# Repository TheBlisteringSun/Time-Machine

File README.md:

# Time-Machine
Deceptively small macropad (could fit in your palm)

Time Machine is a KMK-powered, 6-key + Rotary Encoder, OLED display, Macropad with underglow lighting. 

KMK firmware for the custom Hackpad
-----------------------------------
Features
~~~~~~~~
* Constants at the top define which matrix key does what—easy to tweak later.
* A sleep toggle (OLED off, inputs ignored until woken).
* EC11 rotary encoder (GP8=A, GP9=B, GP10=SW)
    * Short‑press once → enter **Timer‑Setup** mode
    * Turn knob → cycle through preset durations
      (1, 5, 10, 15, 20, 30, 40 minutes)
    * Short‑press again → start the countdown
* 0.91″ SSD1306 OLED (I²C on GP6=SDA, GP7=SCL)
    * Shows selected duration or live progress bar + remaining time
* 3× SK6812 LEDs daisy‑chained on GP5 (optional flash on timer end)
* Stores a persistent points counter in /points.txt and flashes the LEDs:
    * +1 → yellow flash
    * +2 → purple for 1 minute
    * negative actions → blue flash
 * Two under‑glow LEDs stay dim green whenever no other colour is flashing.
~~~~~~~~~~

Requires:
* CircuitPython ≥ 9.0 or RP2040‑UF2 w/ displayio support
* `adafruit_displayio_ssd1306` and `adafruit_display_text` libraries in /lib
* KMK (copy kmk/ into CIRCUITPY drive)

Save this file as `code.py` or `main.py` on the XIAO‑RP2040.

# Design
This was my first time doing a hardware project! Thanks to all the friends that I bugged constantly :P

## PCB
I learned how to use a matrix to get all my features onto the XIAO microcontroller perfectly

The schematic and the PCB were made in KiCad

## Case
First time CADing too! It ain't much, but it's honest work.

Case was made using Autodesk Fusion

## Firmware
Time Machine was made with custom-coded firmware written with the KMK library in Python

# BOM
*6 cans of redbull not included

## Electronics
* 1x XIAO RP2040
* 1x EC11E Rotary Encoder (with switch)
* 1x Rotary Encoder Knob
* 1x 0.91" OLED Display
* 6x Cherry MX Switches
* 6x Blank DSA Keycaps
* 6x Diode (THT)
* 3x SK6812 Mini LEDs
* 1x 330 Ohm Resistor

## Case
* 1x case_top.stl
* 1x case_plt.stl
* 1x case_btm.stl
* 3x M3x16 screw
* 4x 10mm Rubber Feet
* 3x M3x5x4mm heatset inserts

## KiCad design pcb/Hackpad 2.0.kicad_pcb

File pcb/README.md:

# PCB
This file contains all the libraries used to make the PCB for the Time Machine

The gerbers.zip file to make your own PCB can be found in \production

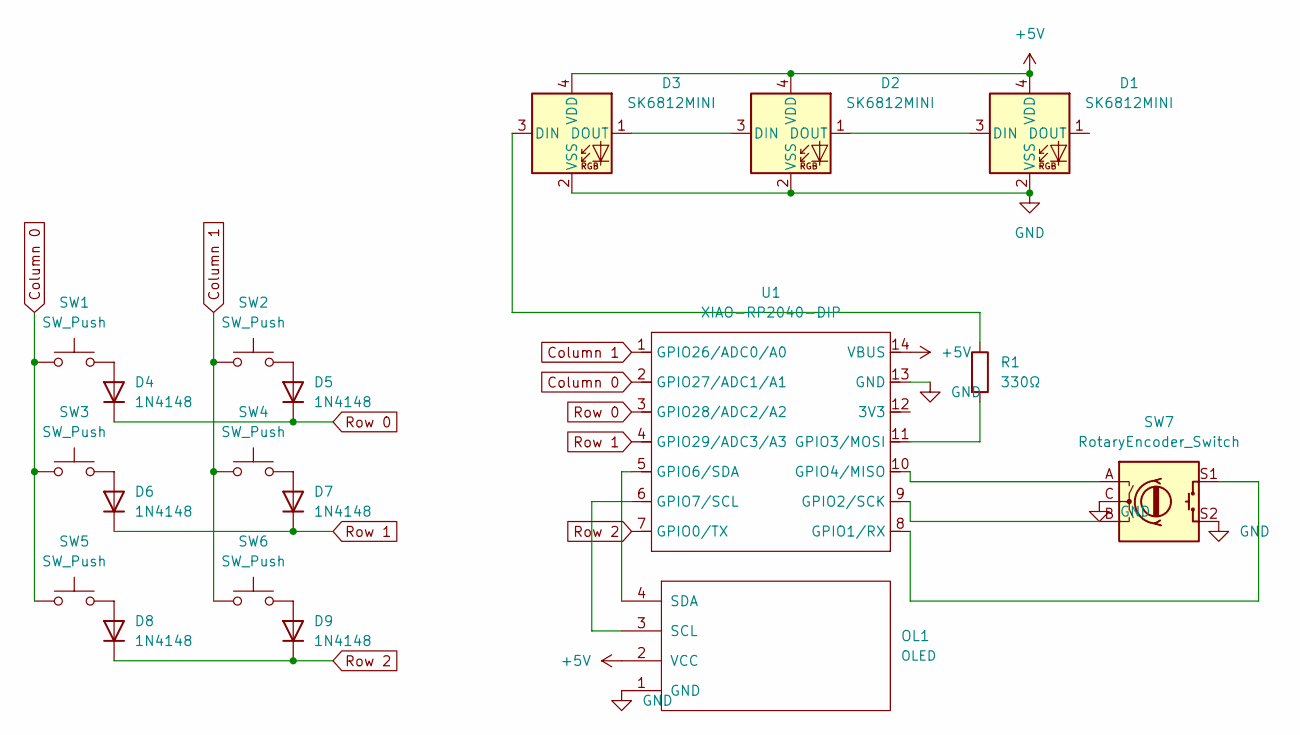
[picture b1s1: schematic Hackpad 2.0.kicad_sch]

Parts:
D1, D2, D3: SK6812MINI; LED_SK6812MINI_PLCC4_3.5x3.5mm_P1.75mm
D4, D5, D6, D7, D8, D9: 1N4148; D_DO-35_SOD27_P7.62mm_Horizontal
OL1: OLED; SSD1306-0.91-OLED-4pin-128x32
R1: 330Ω; R_Axial_DIN0207_L6.3mm_D2.5mm_P7.62mm_Horizontal
SW1, SW2, SW3, SW4, SW5, SW6: SW_Push; SW_Cherry_MX_1.00u_PCB
SW7: RotaryEncoder_Switch; RotaryEncoder_Alps_EC11E-Switch_Vertical_H20mm
U1: XIAO-RP2040-DIP

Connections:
+5V: D1.4 (VDD), D2.4 (VDD), D3.4 (VDD), OL1.2 (VCC), U1.14 (VBUS)
Column 0: SW1.1, SW3.1, SW5.1, U1.2 (GPIO27/ADC1/A1)
Column 1: SW2.1, SW4.1, SW6.1, U1.1 (GPIO26/ADC0/A0)
GND: D1.2 (VSS), D2.2 (VSS), D3.2 (VSS), OL1.1 (GND), SW7.C, SW7.S2, U1.13 (GND)
unnamed: D1.3 (DIN), D2.1 (DOUT)
unnamed: D2.3 (DIN), D3.1 (DOUT)
unnamed: D3.3 (DIN), R1.1
unnamed: D4.2 (A), SW1.2
unnamed: D5.2 (A), SW2.2
unnamed: D6.2 (A), SW3.2
unnamed: D7.2 (A), SW4.2
unnamed: D8.2 (A), SW5.2
unnamed: D9.2 (A), SW6.2
unnamed: OL1.3 (SCL), U1.6 (GPIO7/SCL)
unnamed: OL1.4 (SDA), U1.5 (GPIO6/SDA)
unnamed: SW7.S1, U1.8 (GPIO1/RX)
unnamed: SW7.B, U1.9 (GPIO2/SCK)
unnamed: R1.2, U1.11 (GPIO3/MOSI)
unnamed: SW7.A, U1.10 (GPIO4/MISO)
Row 0: D4.1 (K), D5.1 (K), U1.3 (GPIO28/ADC2/A2)
Row 1: D6.1 (K), D7.1 (K), U1.4 (GPIO29/ADC3/A3)
Row 2: D8.1 (K), D9.1 (K), U1.7 (GPIO0/TX)

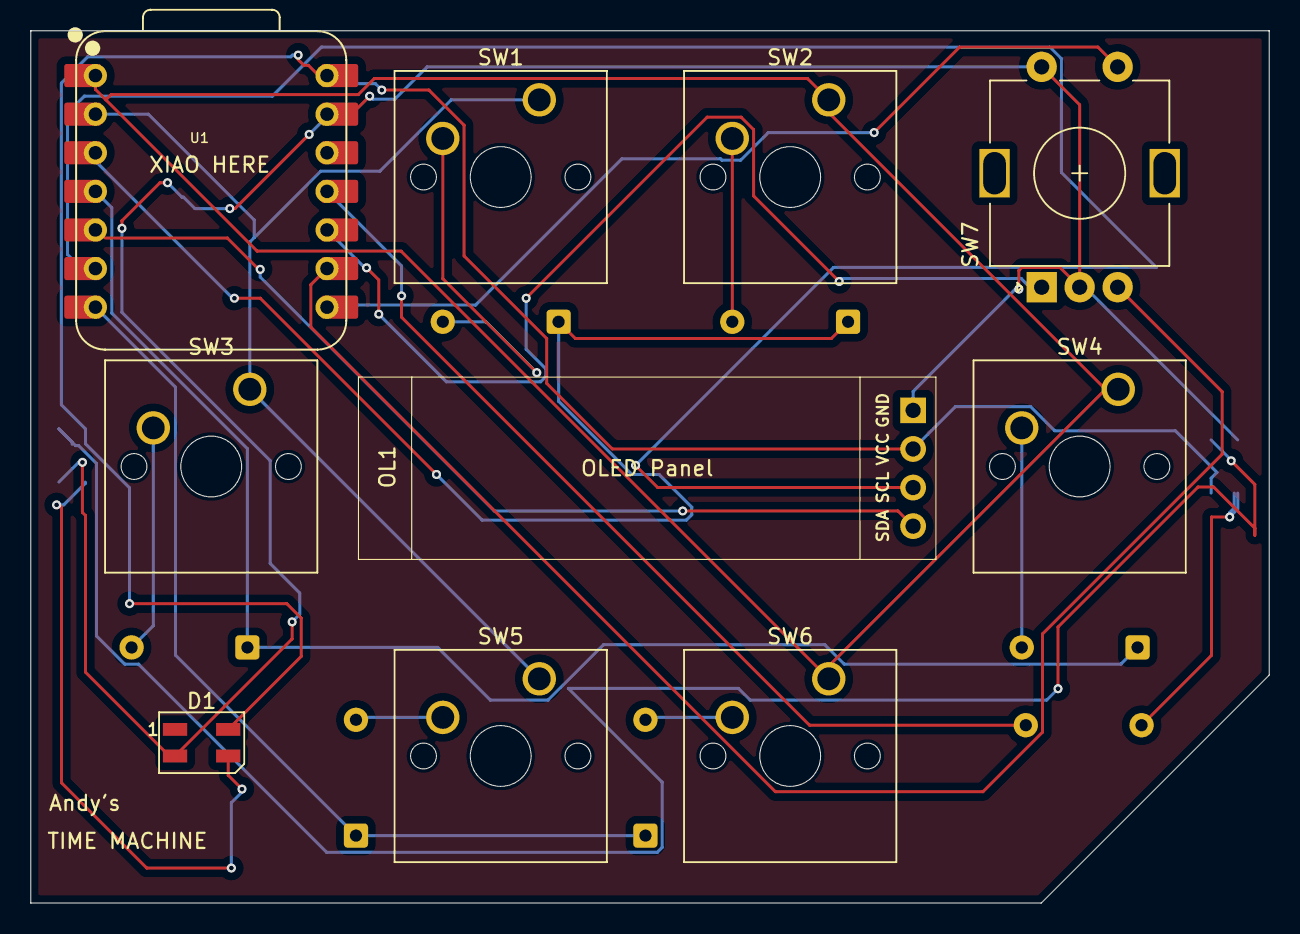
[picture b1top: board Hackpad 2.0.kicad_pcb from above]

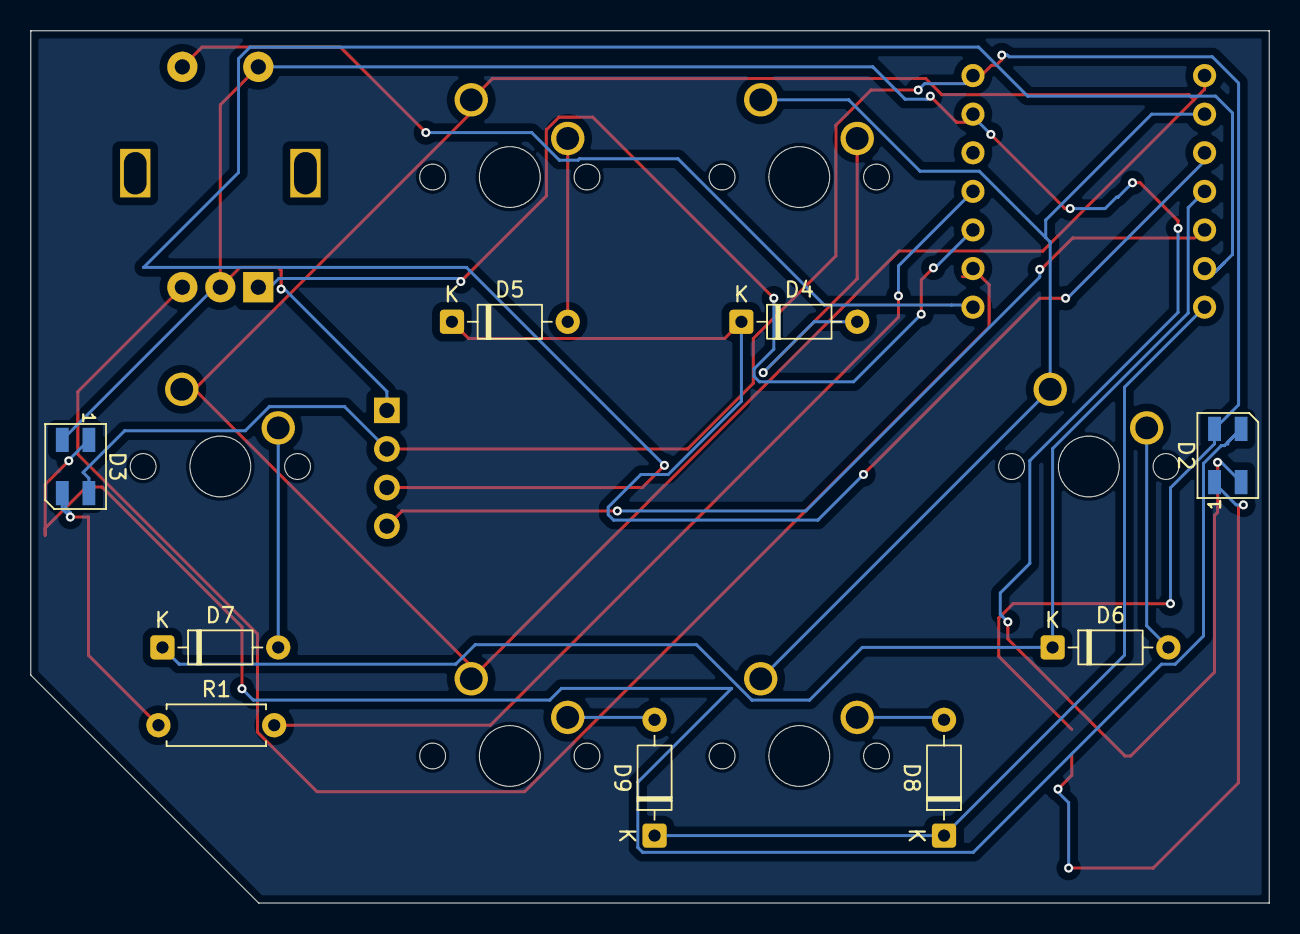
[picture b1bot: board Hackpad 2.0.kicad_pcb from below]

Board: 2 copper layers, 81.5 x 57.4 mm, 19 parts (9 on the bottom side), 22 nets.

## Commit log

2025-06-16 update features
2025-06-16 Update README.md
    PCB, Case, Firmware, BOM
2025-06-16 Add gerbers file
2025-06-16 Rename gerbers.zip to production/gerbers.zip
2025-06-16 add headset inserts
2025-06-16 add case
2025-06-16 Update and rename main.py to code.py
    Add functions to each button + Sleep + underglow
2025-06-16 Add PCB
2025-06-16 Upload PCB
2025-06-16 Add Cad
